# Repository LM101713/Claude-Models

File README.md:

# Claude-Models

3D-printable models and the procedural Blender scripts that generate them.

## Odd Layer Product 001: FILAMENT PATH (direction approved; collecting measurements)

A research and engineering specification for a **fixed-radius, external-only AMS-to-printer PTFE
tube routing system** for Bambu Lab P1S / X1 and H2S / H2C / H2D printers. It has shared
snap-on R80 bend formers, machine-specific anchors on Bambu's own rear mounts, a radius gauge, a
square-cut tube jig, and a published pull-force test. The report covers market research, a
ranked comparison of seven opportunities, a printer compatibility matrix, design rules,
tolerances, risks, a physical test protocol and a MakerWorld launch plan. **No CAD exists yet.**
Building starts only after owner approval.

- Research report: [`filament-path/README.md`](filament-path/README.md)
- Owner refinements, radius validation plan, pull-force protocol, MakerWorld plan: [`filament-path/REVISION_01.md`](filament-path/REVISION_01.md)
- Measurement guide (current step) and template: [`filament-path/MEASUREMENT_GUIDE.md`](filament-path/MEASUREMENT_GUIDE.md), [`filament-path/measurements_template.csv`](filament-path/measurements_template.csv)

## Odd Layer HF-04 HOLDFAST

A **wall grip for brooms, mops and long tools** that locks by itself. Push the handle in and
up, then let go: two orange rollers on 16° ramps are dragged down into a narrowing wedge by the
tool's own weight, so the heavier the tool, the harder it is held. Lift the handle and it lets
go. One size takes 19–32 mm handles. It has three printed parts (a base and two identical
rollers), no springs, no press fits and no supports. Each roller is captive on a stub in a
keyhole T-slot. A 10-minute fit coupon and a Loose roller variant cover printers that print
holes tight. It is generated by a parametric script (manifold3d geometry, Blender project and
renders) that also runs 32 checks: interference over the full travel, assembly path,
retention, handle range, four printer-variation corners, overhangs, and every exported file
re-read from disk. CAD-validated only: not
yet printed.

- Generator: [`holdfast/holdfast.py`](holdfast/holdfast.py) + [`holdfast/hf/`](holdfast/hf)
- Concept study, engineering report, assembly, print settings, physical test plan: [`holdfast/README.md`](holdfast/README.md)
- Validation report: [`holdfast/models/HF04_validation_report.md`](holdfast/models/HF04_validation_report.md)
- Print files: [`holdfast/models/`](holdfast/models/)

## Odd Layer ML-02 MotionLoop

A hand-cranked **desk mechanism**. One crank drives two opposed sliders through two
connecting rods, and everything that moves is in plain view. The crank is a built-up
two-throw crankshaft (cheek · wheel · cheek) running in two towers. The sliders run in 45°
dovetail grooves in a graphite plinth. The default MIRROR wheel puts the pins 180° apart, so
the sliders breathe out and in together. The optional SHUTTLE wheel puts them in line, so one
slider moves out while the other moves in. It is 13 printed parts (9 designs), with no
hardware and no supports. It is generated by a modular, parametric Blender script that also
sweeps the mechanism through a full turn (0 collisions), measures every fit, and exports STL,
3MF, an editable .blend and renders. CAD-validated only: not yet printed.

- Scripts: [`motionloop/motionloop.py`](motionloop/motionloop.py) + [`motionloop/ml/`](motionloop/ml) (Blender / bpy)
- Mechanism study, dimensions, tolerances, Bambu Studio settings, assembly, weak points, test plan: [`motionloop/README.md`](motionloop/README.md)
- Validation report: [`motionloop/models/ML02_validation_report.md`](motionloop/models/ML02_validation_report.md)
- Print files: [`motionloop/models/`](motionloop/models/)

## Odd Layer SL-01 SlideLock

A pocket **slider fidget** whose whole point is the feel: _tick · tick · tick · LOCK_. An
orange knob runs 20 mm along a graphite body, with three light detents in the middle and a
firm lock at each end. At each end the spring holds the carriage against a hard stop, so
there is no rattle. Inside are two in-plane cantilever leaf springs on a captured carriage,
running in V-notch tracks in the walls. It has three printed parts, no hardware and no
supports, plus Soft / Standard / Firm carriages. It is generated by one parametric Blender
script that also checks every fit, sweeps the full travel with the springs bent to a detent
model, and exports STL, 3MF, an editable .blend and renders. CAD-validated only: not yet
printed.

- Script: [`slidelock/slidelock.py`](slidelock/slidelock.py) (Blender / bpy)
- Concept, mechanism study, engineering, print settings, assembly, risks and prototype plan: [`slidelock/README.md`](slidelock/README.md)
- Validation report: [`slidelock/models/SL01_validation_report.md`](slidelock/models/SL01_validation_report.md)
- Print files: [`slidelock/models/`](slidelock/models/)

## DRYDOCK Prototype 001

A refillable **desiccant cartridge for the hub of a filament spool**. It has a vented body, two
quarter-turn QuickLock caps with a detent click and a hard stop, replaceable indicator
windows, and spring-centring adapters for 51–61 mm spool bores. It uses six printed parts,
no hardware and no supports. It is generated by a parametric build123d script that checks
every fit with boolean geometry and exports STEP, STL and 3MF. CAD-validated only: not yet
printed.

- Script: [`drydock/drydock.py`](drydock/drydock.py)
- Engineering analysis, assembly, print settings and test plan: [`drydock/README.md`](drydock/README.md)
- Validation report: [`drydock/models/DD001_validation_report.md`](drydock/models/DD001_validation_report.md)
- Print files: [`drydock/models/`](drydock/models/)

## Cutaway Turbofan

A display model that **shows how a jet engine works**: a high-bypass turbofan with a quarter
of every casing cut away. Turn the spinner and the fan, six compressor stages and four turbine
stages turn together on one shaft. The stand spells out SUCK · SQUEEZE · BANG · BLOW. It has
20 printed parts, needs no supports and no screws, and is generated by a pure-Python script
(manifold3d) that also checks overhangs and every running clearance.

- Script: [`cutaway-turbofan/cutaway_turbofan.py`](cutaway-turbofan/cutaway_turbofan.py)
- How it works, printing and assembly: [`cutaway-turbofan/README.md`](cutaway-turbofan/README.md)
- Ready-to-print plates: [`cutaway-turbofan/models/`](cutaway-turbofan/models/)

## Gemscale Flexi Dragon

A low-poly, winged, articulated dragon that **prints in one piece with no supports**. It is
generated entirely by one Blender script, which also exports STL/3MF files, checks
printability, and renders cover images.

- Script: [`gemscale-dragon/gemscale_dragon.py`](gemscale-dragon/gemscale_dragon.py)
- How to use it: [`gemscale-dragon/README.md`](gemscale-dragon/README.md)
- Ready-to-print files: [`gemscale-dragon/models/`](gemscale-dragon/models/)
- MakerWorld listing kit: [`gemscale-dragon/MAKERWORLD_LISTING.md`](gemscale-dragon/MAKERWORLD_LISTING.md)

## Gemscale Flexi Octopus

A cute, faceted, articulated octopus that **prints in one piece with no supports** and is quick
to print (the mini takes about 40 minutes). It uses the same joint as the dragon. It's
generated by a pure-Python script (manifold3d, no Blender needed), which also checks
printability and exports STL/3MF files. A three.js studio renders the cover images.

- Script: [`gemscale-octopus/gemscale_octopus.py`](gemscale-octopus/gemscale_octopus.py)
- How to use it: [`gemscale-octopus/README.md`](gemscale-octopus/README.md)
- Ready-to-print files: [`gemscale-octopus/models/`](gemscale-octopus/models/)
- MakerWorld listing kit: [`gemscale-octopus/MAKERWORLD_LISTING.md`](gemscale-octopus/MAKERWORLD_LISTING.md)

## Gemscale Flexi Bat

A faceted Halloween bat that **prints in one piece with no supports**. It has slit-pupil
eyes, cupped ears, fangs, a wiggly abdomen, and real bat wings: arm, forearm and a hand of
four clawed fingers fanning out, all jointed so they fold back and forth. The keychain version hangs upside down by its tail. It uses the same
joint and the same pure-Python toolchain as the octopus.

- Script: [`gemscale-bat/gemscale_bat.py`](gemscale-bat/gemscale_bat.py)
- How to use it: [`gemscale-bat/README.md`](gemscale-bat/README.md)
- Ready-to-print files: [`gemscale-bat/models/`](gemscale-bat/models/)
- MakerWorld listing kit: [`gemscale-bat/MAKERWORLD_LISTING.md`](gemscale-bat/MAKERWORLD_LISTING.md)

## Gemscale Flexi T-Rex

A classic flexi T. rex that **prints in one piece with no supports**: a big toothy head, a
chain of ridged segments with tiny arms and big legs, and a long wiggly tail. Every joint
wiggles side to side. It's generated by a Blender script.

- Script: [`gemscale-trex/gemscale_trex.py`](gemscale-trex/gemscale_trex.py) (Blender)
- How to use it: [`gemscale-trex/README.md`](gemscale-trex/README.md)
- Ready-to-print files: [`gemscale-trex/models/`](gemscale-trex/models/)
- MakerWorld listing kit: [`gemscale-trex/MAKERWORLD_LISTING.md`](gemscale-trex/MAKERWORLD_LISTING.md)

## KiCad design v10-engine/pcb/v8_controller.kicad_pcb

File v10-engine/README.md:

# V10 Display Engine: original, motorized, 90 deg V10

> **Start here: [`PRINT_THIS_FIRST/`](PRINT_THIS_FIRST/README.md)**: the fit-test plate, its Bambu Studio settings and the tests. Print it before any engine part.

An original F1-style naturally aspirated V10 display model, about 340 mm long
on a 400 x 280 mm display base. Working split-pin crankshaft, 10 con-rods on
ball bearings, 10 floating pistons on stainless guide rails (they never touch
their bores), visible through cut-away cylinder windows. A hidden, silent
stepper drives it through a 3:1 belt; three LEDs over every bore flash in the
firing order 1-6-5-10-2-7-3-8-4-9 exactly when each piston reaches the top.

Designed as a premium production piece: **50 units**, years of running, built
by one person with a hex key, a soldering iron and a small vise.

**Everything is generated from code.** Every dimension, fit and clearance lives
in [`config.py`](config.py); the firmware's engine timing is generated from the
same file. If something must change, change a number there and rebuild. Never
edit an STL by hand.

## Status

| Phase | Content | Status |
|---|---|---|
| 1 | Crankcase, valley beam, banks, end plates, crank, rods, pistons, rails | **complete, verified in CAD** |
| 2 | Motor drive (3:1 GT2 belt), display base | **complete, verified in CAD** |
| 3 | Heads, cam covers, side panels, end covers, intake trumpets + throttle frame, exhausts, coil packs, LED strips | **complete, verified in CAD** |
| 4 | Electronics, wiring diagram, firmware | **complete; firmware compiles, logic unit-tested, timing cross-checked against the CAD** |
| 5 | BOM, assembly instructions, burn-in, QC, maintenance, 50-unit print and production plan | **complete** |

### What has been verified, and what has not

Verified by the tools in this repository (re-run them after any change):

* **Every printed part** sliced with the production settings: no overhang over
  45 deg, no bridge over 25 mm, no unsupported ring ceilings, every part one
  solid, every part under 300 mm (`tools/printcheck.py`, `docs/PRINT_REPORT.md`).
* **No collisions:** every pair of static parts; the drive with both belt
  lengths and the motor at both ends of its slots; every moving part against
  every other part over a full revolution in 6 deg steps; smallest running gaps
  reported (`tools/verify_all.py`, `docs/CLEARANCE_REPORT.md`).
* **The build order works:** each part can travel along its documented
  assembly path to its place without hitting anything (`tools/verify_all.py`).
* **Firmware:** compiles for the ESP32 with pinned library versions, unit tests
  pass on a PC, LED timing = CAD piston TDC for all 10 cylinders, hall magnet
  pocket where the firmware expects it (`tools/check_firmware.py`).
* **Electronics model:** every net closed, every GPIO matches the firmware
  (`tools/electronics.py`).

**Not verifiable without building one:** the real feel of the fits, noise,
motor temperature, LED brightness/look, 48 h endurance. CAD and simulation
remove the design mistakes; they cannot replace a first article. **Build unit
#1 completely and run its 48 h burn-in before committing material and printer
time to the other 49** (see `docs/PRODUCTION_PLAN.md`, gate 1).

## Design-for-manufacturing pass (in progress - read these first)

**Nothing has been printed yet.** The DFM pass turned every guessed fit into a
tested one *before* any engine part is printed:

1. [`docs/AFTER_SCHOOL_SUMMARY.md`](docs/AFTER_SCHOOL_SUMMARY.md) - latest status: what was done, decisions, what is needed next
2. [`fits.py`](fits.py) - **the one file** holding every tolerance / clearance / fit
3. [`docs/COUPON_PRINT_GUIDE.md`](docs/COUPON_PRINT_GUIDE.md) - print the 15 coupons first (each < 25 min)
4. [`docs/TEST_CHECKLIST.md`](docs/TEST_CHECKLIST.md) - what to measure, which number to change
5. [`docs/DECISIONS.md`](docs/DECISIONS.md), [`docs/DFM_PHASE0.md`](docs/DFM_PHASE0.md), [`docs/RISKS_FIRST_ENGINE.md`](docs/RISKS_FIRST_ENGINE.md)
6. [`docs/PROTO_BOM.md`](docs/PROTO_BOM.md) - the only order to place until engine #1 runs

## Start here

1. [`docs/DESIGN_NOTES.md`](docs/DESIGN_NOTES.md) - why it is built this way
2. [`docs/BOM.md`](docs/BOM.md) - everything to buy, print and machine, costs x1 / x50
3. [`docs/PRODUCTION_PLAN.md`](docs/PRODUCTION_PLAN.md) - print plan, printer-hours, timeline for 50
4. [`docs/BUILD_GUIDE.md`](docs/BUILD_GUIDE.md) - **V8 motion test, one picture per step** (build this first);
   [`docs/ASSEMBLY.md`](docs/ASSEMBLY.md) - full build order with checklists (still the V10 text)
   [`docs/PCB_GUIDE.md`](docs/PCB_GUIDE.md) - controller PCB rev A (draft, not ordered)
5. [`docs/ELECTRONICS.md`](docs/ELECTRONICS.md) - wiring, controller board, firmware, bring-up
6. [`docs/BURN_IN.md`](docs/BURN_IN.md), [`docs/QC_CHECKLIST.md`](docs/QC_CHECKLIST.md), [`docs/MAINTENANCE.md`](docs/MAINTENANCE.md)

## Part numbering

| # | Part | Qty | Made by |
|---|---|---|---|
| T1-T8 | fit coupons (15 small prints, print first) | 1 set | print (PLA, then ASA) |
| 01 | crankcase (open-top U) | 1 | print |
| 02 | valley beam | 1 | print |
| 03 | cylinder bank (both identical) | 2 | print |
| 04 | end plate (both identical, 608 bearing) | 2 | print |
| 05 | crank end web | 2 | print |
| 06 | crank segment "54" | 2 | print |
| 07 | crank segment "198" | 2 | print |
| 08 | con-rod | 10 | print |
| 09 | piston | 10 | print |
| 10 | cylinder head (both identical) | 2 | print |
| 11 | cam cover (magnetic) | 2 | print |
| 12 | side panel (magnetic) | 2 | print |
| 13 | intake trumpet | 10 | print (or M05) |
| 14 / 15 | exhaust header bank A / bank B | 1 + 1 | print |
| 16 | coil pack | 10 | print |
| 17 | throttle frame | 1 | print |
| 18 | end cover (magnetic, front + rear identical) | 2 | print |
| 19 / 20 | base front half (motor) / rear half (controls, board) | 1 + 1 | print |
| 21 | base bottom panel (both identical) | 2 | print |
| M01 | split crankpin | 5 | CNC, stainless |
| M02 | main shaft | 2 | CNC, stainless |
| M03 | guide rail 3 x 57 | 10 | cut from ground rod |
| M04 | pulley spacer | 1 | CNC, stainless |
| M05 | intake trumpet, aluminium (optional upgrade of 13) | 10 | CNC |
| M06 | bearing spacer ring 6 x 7.5 x 0.75 | 10 | CNC, stainless |
| P1 / P2 | printable stand-ins for M01 / M02 (early fit tests only) | 5 / 2 | print (PETG) |

**19 unique printed parts** (budget 40, pistons and rods not counted). **One
screw size** in the whole engine: M3 x 8 (92 per engine).

## Folder layout

```
v10-engine/
  config.py            ALL dimensions, fits, firing order, speeds (edit this)
  build_all.py         regenerates every STL/STEP, preview and drawing
  cad/                 the parametric model (CadQuery)
    common.py          helpers: placement, export, crush ribs, bridged steps
    coupons.py         test coupons T1-T8;  partnum.py  engraved part numbers
    crank.py  rods_pistons.py  block.py  styling.py  drive.py  base.py
    assembly.py        full engine at any crank angle, interference checks
  firmware/            ESP32 controller (Arduino IDE / PlatformIO), unit tests
  tools/
    verify_all.py      interference, clearance and assembly-path verification
    printcheck.py      slices every part, overhang/bridge analysis, times, grams
    check_fits.py      fails if a clearance is written inside a part file
    plates.py          coupon + motion-test plates (3MF) for the H2C;  proto_bom.py
    check_firmware.py  firmware vs CAD timing + unit tests
    gen_firmware_config.py  config.py -> firmware/v10_engine/engine_geometry.h
    electronics.py     netlist, pin tables, schematic and wiring drawings
    bom.py             BOM, costs, shopping list
    burnin_logger.py   logs the burn-in of many engines over USB
    render.py  drawings.py  animate.py
  stl/                 numbered STL + STEP for every part (print orientation)
  renders/  drawings/  docs/
```

## Regenerating and re-verifying

**V8 (current variant, `config.py` -> `config_v8.py`):** the visible skin is built in
Blender, the moving core in CadQuery (decision D55). One command runs the whole kit in
order and stops at the first failure, with a log per step in `logs/pipeline/`:

```bash
pip install -r requirements.txt bpy manifold3d rtree pillow   # CadQuery + Blender-as-a-module
python tools/pipeline_v8.py          # lint, firmware, params, core meshes, skin build/export/check,
                                     # mesh interference + rotation, print check, plates, BOMs (~30 min)
python tools/pipeline_v8.py --quick  # same without the slicer pass and the rotation sweep (~8 min)
python tools/pipeline_v8.py --from plates   # restart at a step
```

The individual tools behind it (V8 and V10):

```bash
python config.py                    # summary + self-checks
python build_all.py                 # CAD STL/STEP (core parts; the frozen CAD skin for the V8), renders, drawings
python tools/skin_blender.py --all  # Blender skin: build, export, check, render (see tools/skin/README.md)
python tools/skin_check.py          # skin meshes vs the CAD core: interference, motor travel, rotation
python tools/printcheck.py          # slice + printability (needs PrusaSlicer CLI)
python tools/verify_all.py          # CAD interferences, clearances, assembly paths (~20 min)
python tools/check_firmware.py      # firmware vs CAD + unit tests (needs g++)
python tools/electronics.py         # netlist, tables, drawings
python tools/bom.py                 # BOM, costs, shopping list
```

On a headless Linux machine the renderer needs EGL or OSMesa
(`apt install libegl1 libosmesa6`).

## Key design facts

* 90 deg V; bank A (cylinders 1-5) is the left bank seen from the front and sits
  8 mm ahead of bank B. The crank turns **clockwise seen from the front**.
* Stroke 26 mm, rod 62 mm, piston 44 mm, **cylinder pitch 50 mm** (= 3 LEDs of a
  60/m strip).
* Split crankpins at 18 deg give true 72 deg even firing.
* 2 x 608ZZ main bearings, 10 x 686ZZ big-end bearings, 30 bronze bushings.
* Pistons never touch the bores (0.8 mm gap): they slide on stainless rails.
* Every press fit uses crush ribs: no tolerance tuning, no test print.
* Speed 20-120 RPM, StealthChop: silent.
* Limited edition: a numbered engraved plate (H14, "No. 07 / 50") sits in a bevelled recess
  on the base front (`EDITION_PLATE` in config.py; `enabled=False` for a plain front).

This design is original. It is not based on any team's engine or any existing
model, and it contains no logos or trademarks.

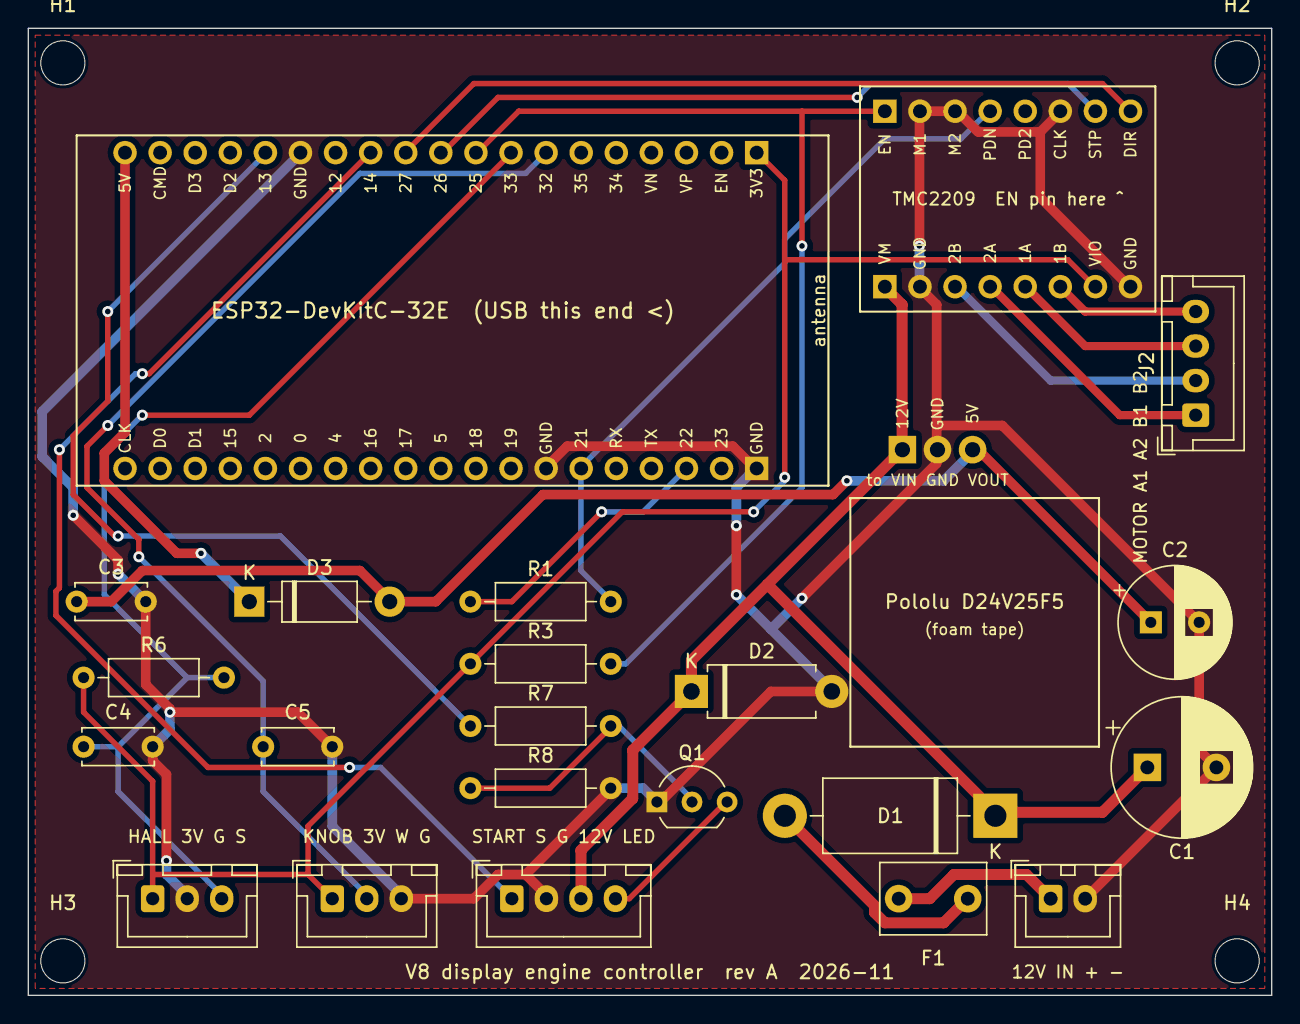
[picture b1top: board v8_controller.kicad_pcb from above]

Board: 2 copper layers, 90.0 x 70.0 mm, 29 parts (0 on the bottom side), 22 nets.

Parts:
C1: 220uF 50V+; CP_Radial_D10.0mm_P5.00mm
C2: 470uF 25V+; CP_Radial_D8.0mm_P3.50mm
C3, C5: 100nF; C_Disc_D5.0mm_W2.5mm_P5.00mm
C4: 10nF; C_Disc_D5.0mm_W2.5mm_P5.00mm
D1: 1N5822; D_DO-201AD_P15.24mm_Horizontal
D2: P6KE18A; D_DO-15_P10.16mm_Horizontal
D3: 1N5817; D_DO-41_SOD81_P10.16mm_Horizontal
F1: PPTC 2A; C_Disc_D7.5mm_W5.0mm_P5.00mm
H1, H2, H3, H4: M3; MountingHole_3.2mm_M3
J1: 12V IN; JST_XH_B2B-XH-A_1x02_P2.50mm_Vertical
J2: MOTOR; JST_XH_B4B-XH-A_1x04_P2.50mm_Vertical
J3: HALL; JST_XH_B3B-XH-A_1x03_P2.50mm_Vertical
J6: KNOB; JST_XH_B3B-XH-A_1x03_P2.50mm_Vertical
J7: START; JST_XH_B4B-XH-A_1x04_P2.50mm_Vertical
Q1: 2N3904; TO-92_Inline_Wide
R1, R7: 1k; R_Axial_DIN0207_L6.3mm_D2.5mm_P10.16mm_Horizontal
R3, R6: 10k; R_Axial_DIN0207_L6.3mm_D2.5mm_P10.16mm_Horizontal
R8: 100k; R_Axial_DIN0207_L6.3mm_D2.5mm_P10.16mm_Horizontal
U1, U1B: ESP32-DevKitC-32E
U2: Pololu D24V25F5 5V
U3, U3B: BTT TMC2209 V1.3

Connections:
12V_F: D1.2, F1.2
12V_IN: F1.1, J1.1
DIR: U1.11, U3.8
DRV_EN: R3.2, U1.9, U3.1
GND: C1.2, C2.2, C3.2, C4.2, C5.2, D2.2, J1.2, J3.2, J6.3, J7.2, Q1.1, R8.2, U1.14, U1B.20, U1B.26, U2.2, U3.2, U3.3, U3.6, U3B.10, U3B.16
HALL: C4.1, J3.3, R6.2, U1.8
KNOB: C5.1, J6.2, U1.7
MOT_A1: J2.1, U3B.12
MOT_A2: J2.2, U3B.11
MOT_B1: J2.3, U3B.13
MOT_B2: J2.4, U3B.14
Q1_BASE: Q1.2, R7.2, R8.1
RING_K: J7.4, Q1.3
RING_PWM: R7.1, U1.15
START: J7.1, U1.12
STEP: U1.10, U3.7
TMC_UART: R1.2, U1B.25, U3.4
UART_TX: R1.1, U1B.22
V3: J3.1, J6.1, R3.1, R6.1, U1.1, U3B.15
V5: C2.1, C3.1, D3.2, U2.3
V5_MCU: D3.1, U1.19
V12: C1.1, D1.1, D2.1, J7.3, U2.1, U3B.9
